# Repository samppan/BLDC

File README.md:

# BLDC

## BLDC Motor Driver Architecture
3 key building blocks for BLDC motor driver are: 
1. Motor controller, typically a MCU
2. Gate Drivers; PWM input, output drives half-bridges
3. Power MOSFET in half-bridges
4. Senseored feedback

<figcaption>Source: TI</figcaption>

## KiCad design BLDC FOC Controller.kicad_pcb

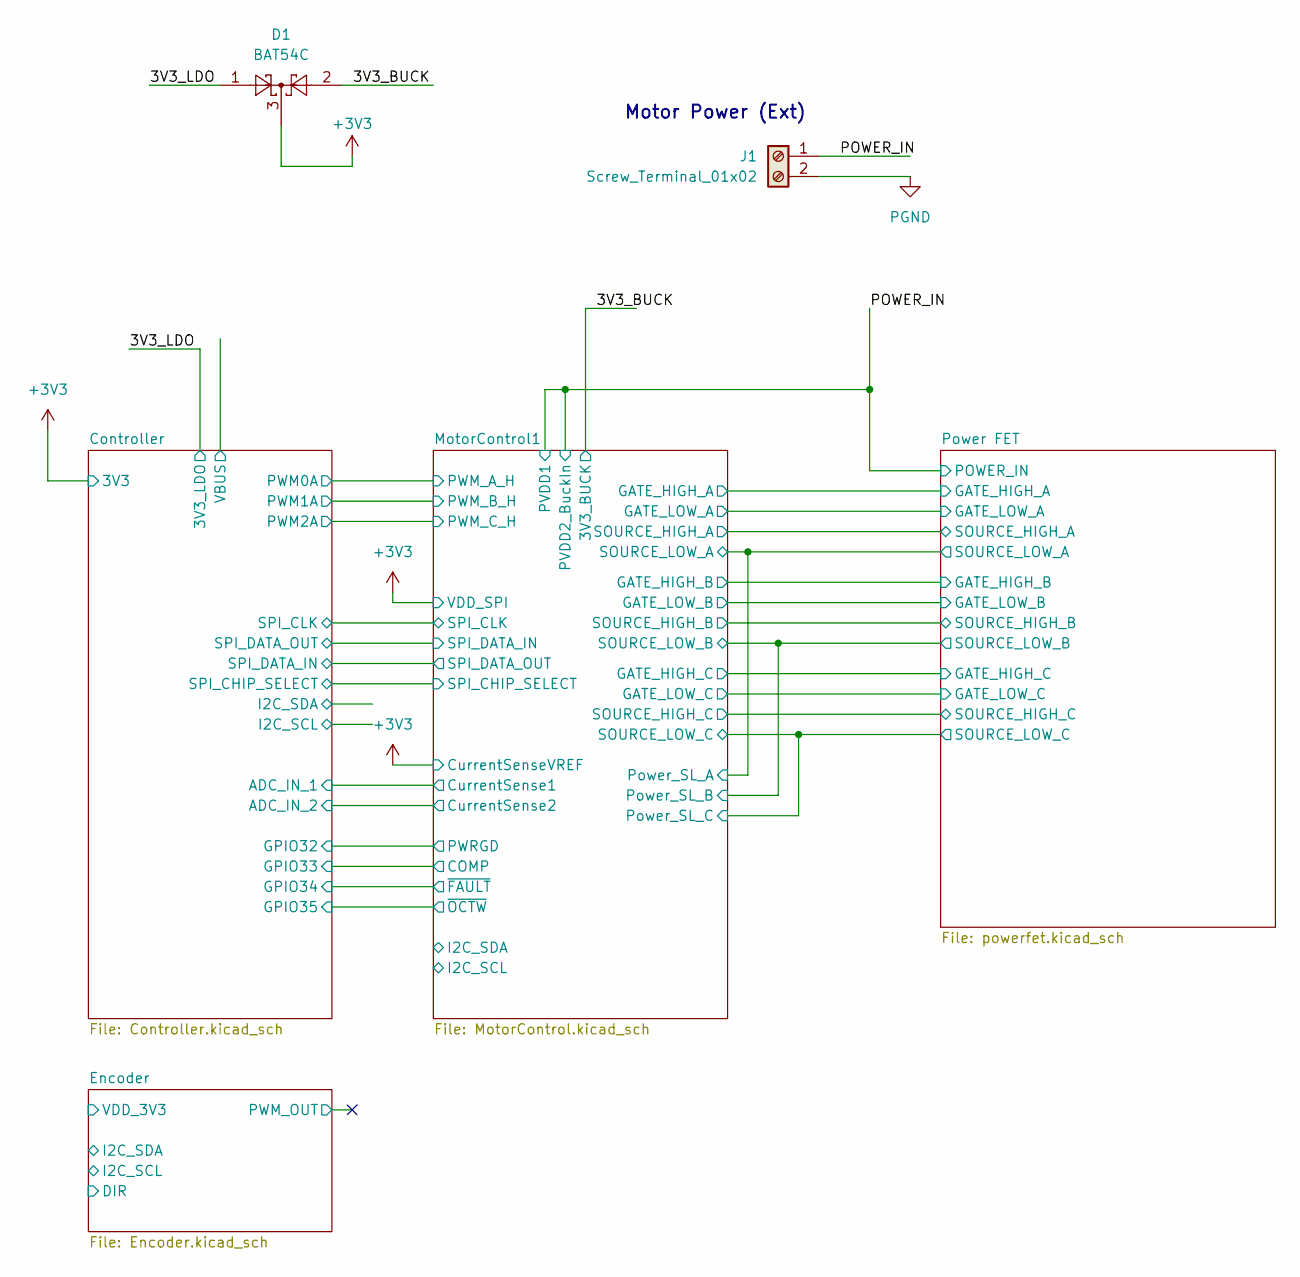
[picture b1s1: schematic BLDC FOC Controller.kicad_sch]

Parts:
D1: BAT54C; SOT-23
J1: Screw_Terminal_01x02; TerminalBlock_TE_282834-2_1x02_P2.54mm_Horizontal

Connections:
/3V3_BUCK: D1.2; also elsewhere on the board
/3V3_LDO: D1.1; also elsewhere on the board
/POWER_IN: J1.1; also elsewhere on the board
GNDA: J1.2; also elsewhere on the board

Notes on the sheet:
Motor Power (Ext)

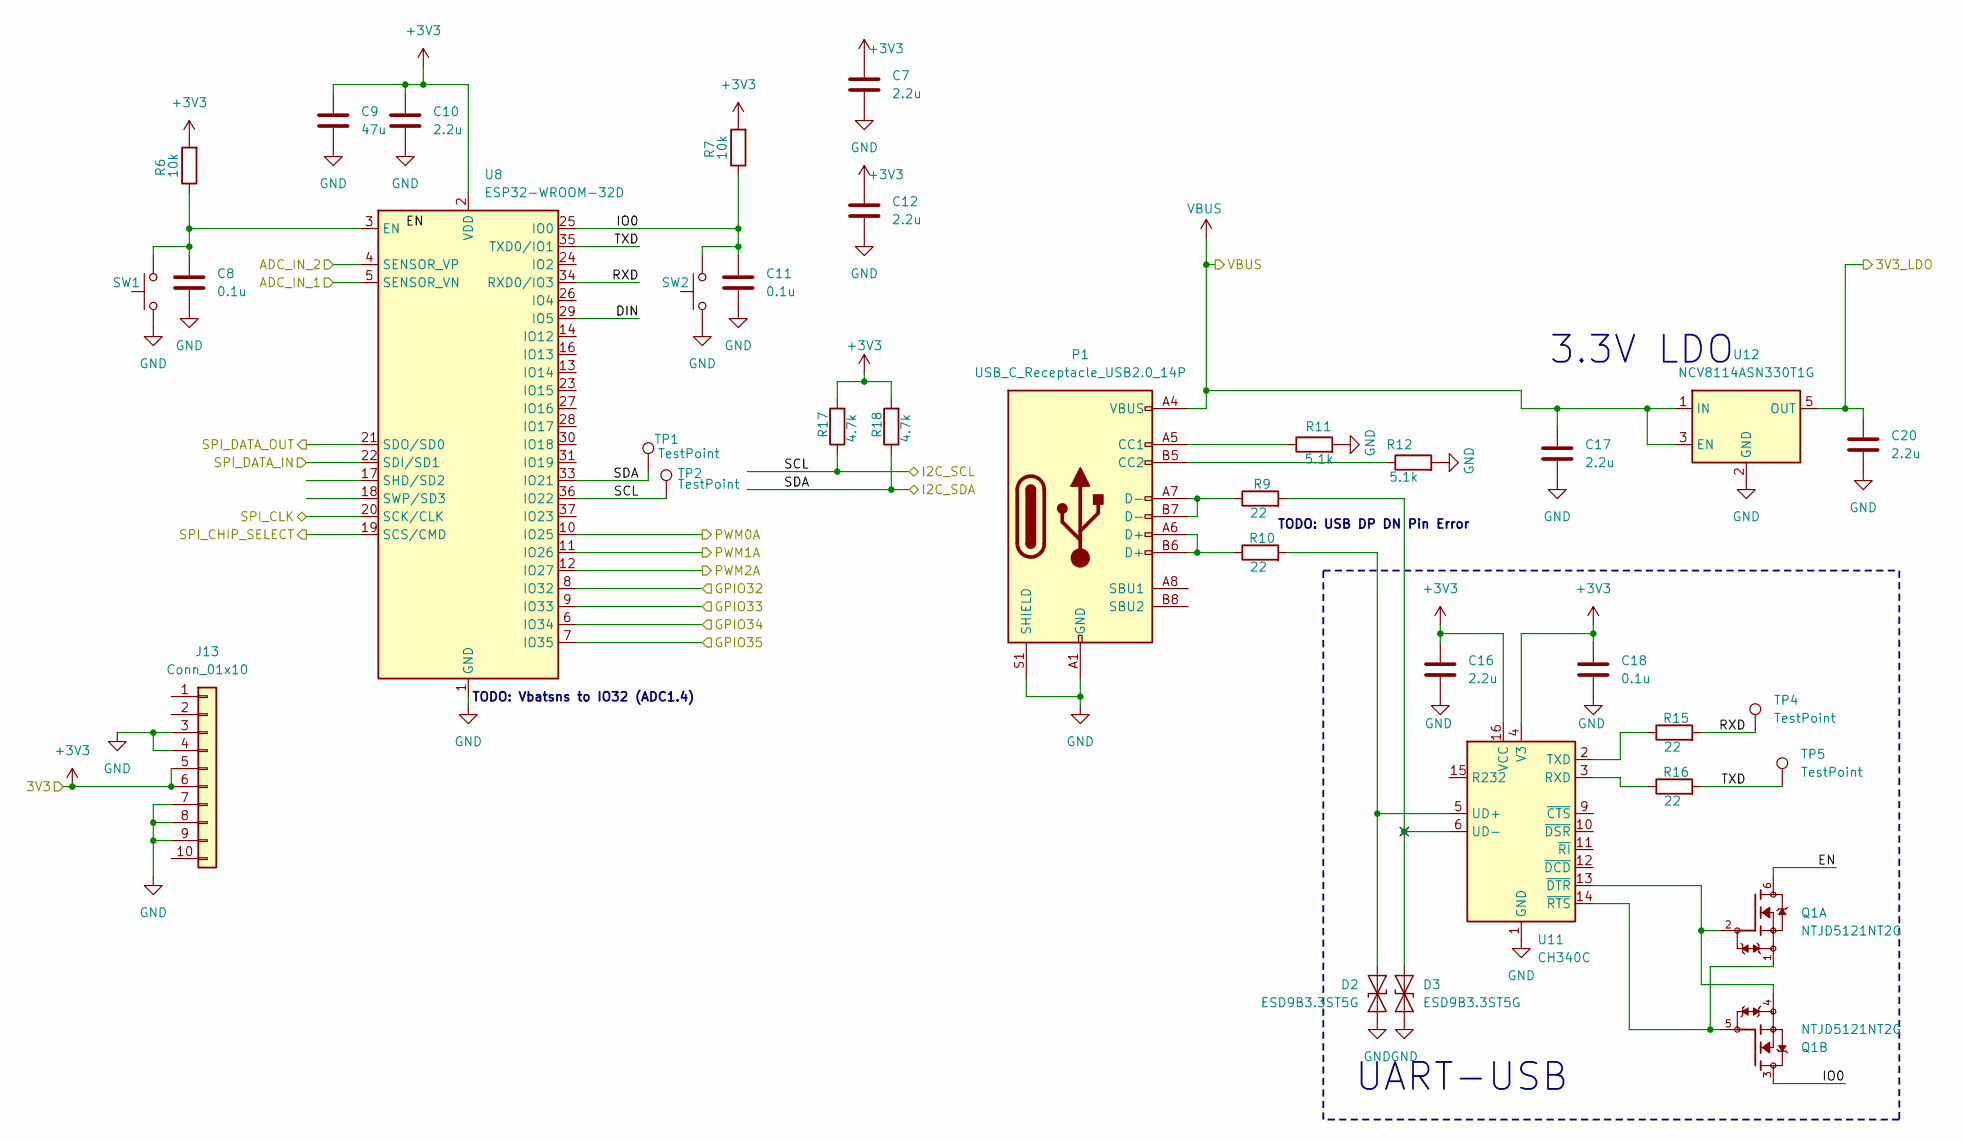
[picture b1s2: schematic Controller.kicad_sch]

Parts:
C7, C10, C12, C16, C17, C20: 2.2u; C_0603_1608Metric_Pad1.08x0.95mm_HandSolder
C8, C11, C18: 0.1u; C_0603_1608Metric_Pad1.08x0.95mm_HandSolder
C9: 47u; C_1206_3216Metric_Pad1.33x1.80mm_HandSolder
D2, D3: ESD9B3.3ST5G; D_SOD-923
J13: Conn_01x10; PinSocket_1x10_P2.54mm_Vertical
P1: USB_C_Receptacle_USB2.0_14P; USB_C_Receptacle_JAE_DX07S016JA1R1500
Q1: NTJD5121NT2G; SOT65P210X110-6N; PARTREV 9
R6, R7: 10k; R_0603_1608Metric_Pad0.98x0.95mm_HandSolder
R9, R10, R15, R16: 22; R_0603_1608Metric_Pad0.98x0.95mm_HandSolder
R11, R12: 5.1k; R_0603_1608Metric_Pad0.98x0.95mm_HandSolder
R17, R18: 4.7k; R_0603_1608Metric_Pad0.98x0.95mm_HandSolder
SW1, SW2: SW_Push_SPST_NO_Alps_SKRK
TP1, TP2, TP4, TP5: TestPoint; TestPoint_Pad_D1.5mm
U8: ESP32-WROOM-32D
U11: CH340C; SOIC-16_3.9x9.9mm_P1.27mm
U12: NCV8114ASN330T1G; TSOT-23-5

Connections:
/3V3_LDO: C20.1, U12.5 (OUT); also elsewhere on the board
/Controller/DIN: U8.29 (IO5)
/Controller/IO0: C11.1, Q1.3, R7.1, SW2.2, U8.25 (IO0)
/Controller/RXD: R15.2, TP4.1, U8.34 (RXD0/IO3)
/Controller/SCL: R17.1, TP2.1, U8.36 (IO22)
/Controller/SDA: R18.1, TP1.1, U8.33 (IO21)
/Controller/TXD: R16.2, TP5.1, U8.35 (TXD0/IO1)
/MotorControl1/COMP: U8.9 (IO33); also elsewhere on the board
/MotorControl1/INH_A: U8.10 (IO25); also elsewhere on the board
/MotorControl1/INH_B: U8.11 (IO26); also elsewhere on the board
/MotorControl1/INH_C: U8.12 (IO27); also elsewhere on the board
/MotorControl1/PWRGD: U8.8 (IO32); also elsewhere on the board
/MotorControl1/SCLK: U8.20 (SCK/CLK); also elsewhere on the board
/MotorControl1/SDI: U8.21 (SDO/SD0); also elsewhere on the board
/MotorControl1/SDO: U8.22 (SDI/SD1); also elsewhere on the board
/MotorControl1/SO1: U8.5 (SENSOR_VN); also elsewhere on the board
/MotorControl1/SO2: U8.4 (SENSOR_VP); also elsewhere on the board
/MotorControl1/~FAULT: U8.6 (IO34); also elsewhere on the board
/MotorControl1/~OCTW: U8.7 (IO35); also elsewhere on the board
/MotorControl1/~SCS: U8.19 (SCS/CMD); also elsewhere on the board
GND: C7.2, C8.2, C9.2, C10.2, C11.2, C12.2, C16.2, C17.2, C18.2, C20.2, D2.1 (A1), D3.1 (A1), J13.3, J13.4, J13.7, J13.8, J13.9, P1.A1 (GND), P1.A12 (GND), P1.B1 (GND), P1.B12 (GND), P1.S1 (SHIELD), R11.2, R12.2, SW1.1, SW2.1, U8.1 (GND), U8.15 (GND), U8.38 (GND), U8.39 (GND), U11.1 (GND), U12.2 (GND); also elsewhere on the board
unnamed: D2.2 (A2), R10.2, U11.5 (UD+)
unnamed: P1.A5 (CC1), R11.1
unnamed: P1.B5 (CC2), R12.1
unnamed: P1.A6 (D+), P1.B6 (D+), R10.1
unnamed: P1.A7 (D-), P1.B7 (D-), R9.1
unnamed: C8.1, R6.1, SW1.2, U8.3 (EN)
unnamed: R16.1, U11.3 (RXD)
unnamed: R15.1, U11.2 (TXD)
unnamed: Q1.2, Q1.4, U11.13 (~DTR)
unnamed: Q1.1, Q1.5, U11.14 (~RTS)
VBUS: C17.1, P1.A4 (VBUS), P1.A9 (VBUS), P1.B4 (VBUS), P1.B9 (VBUS), U12.1 (IN), U12.3 (EN)

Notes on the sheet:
UART-USB
3.3V LDO
TODO: Vbatsns to IO32 (ADC1.4)
TODO: USB DP DN Pin Error

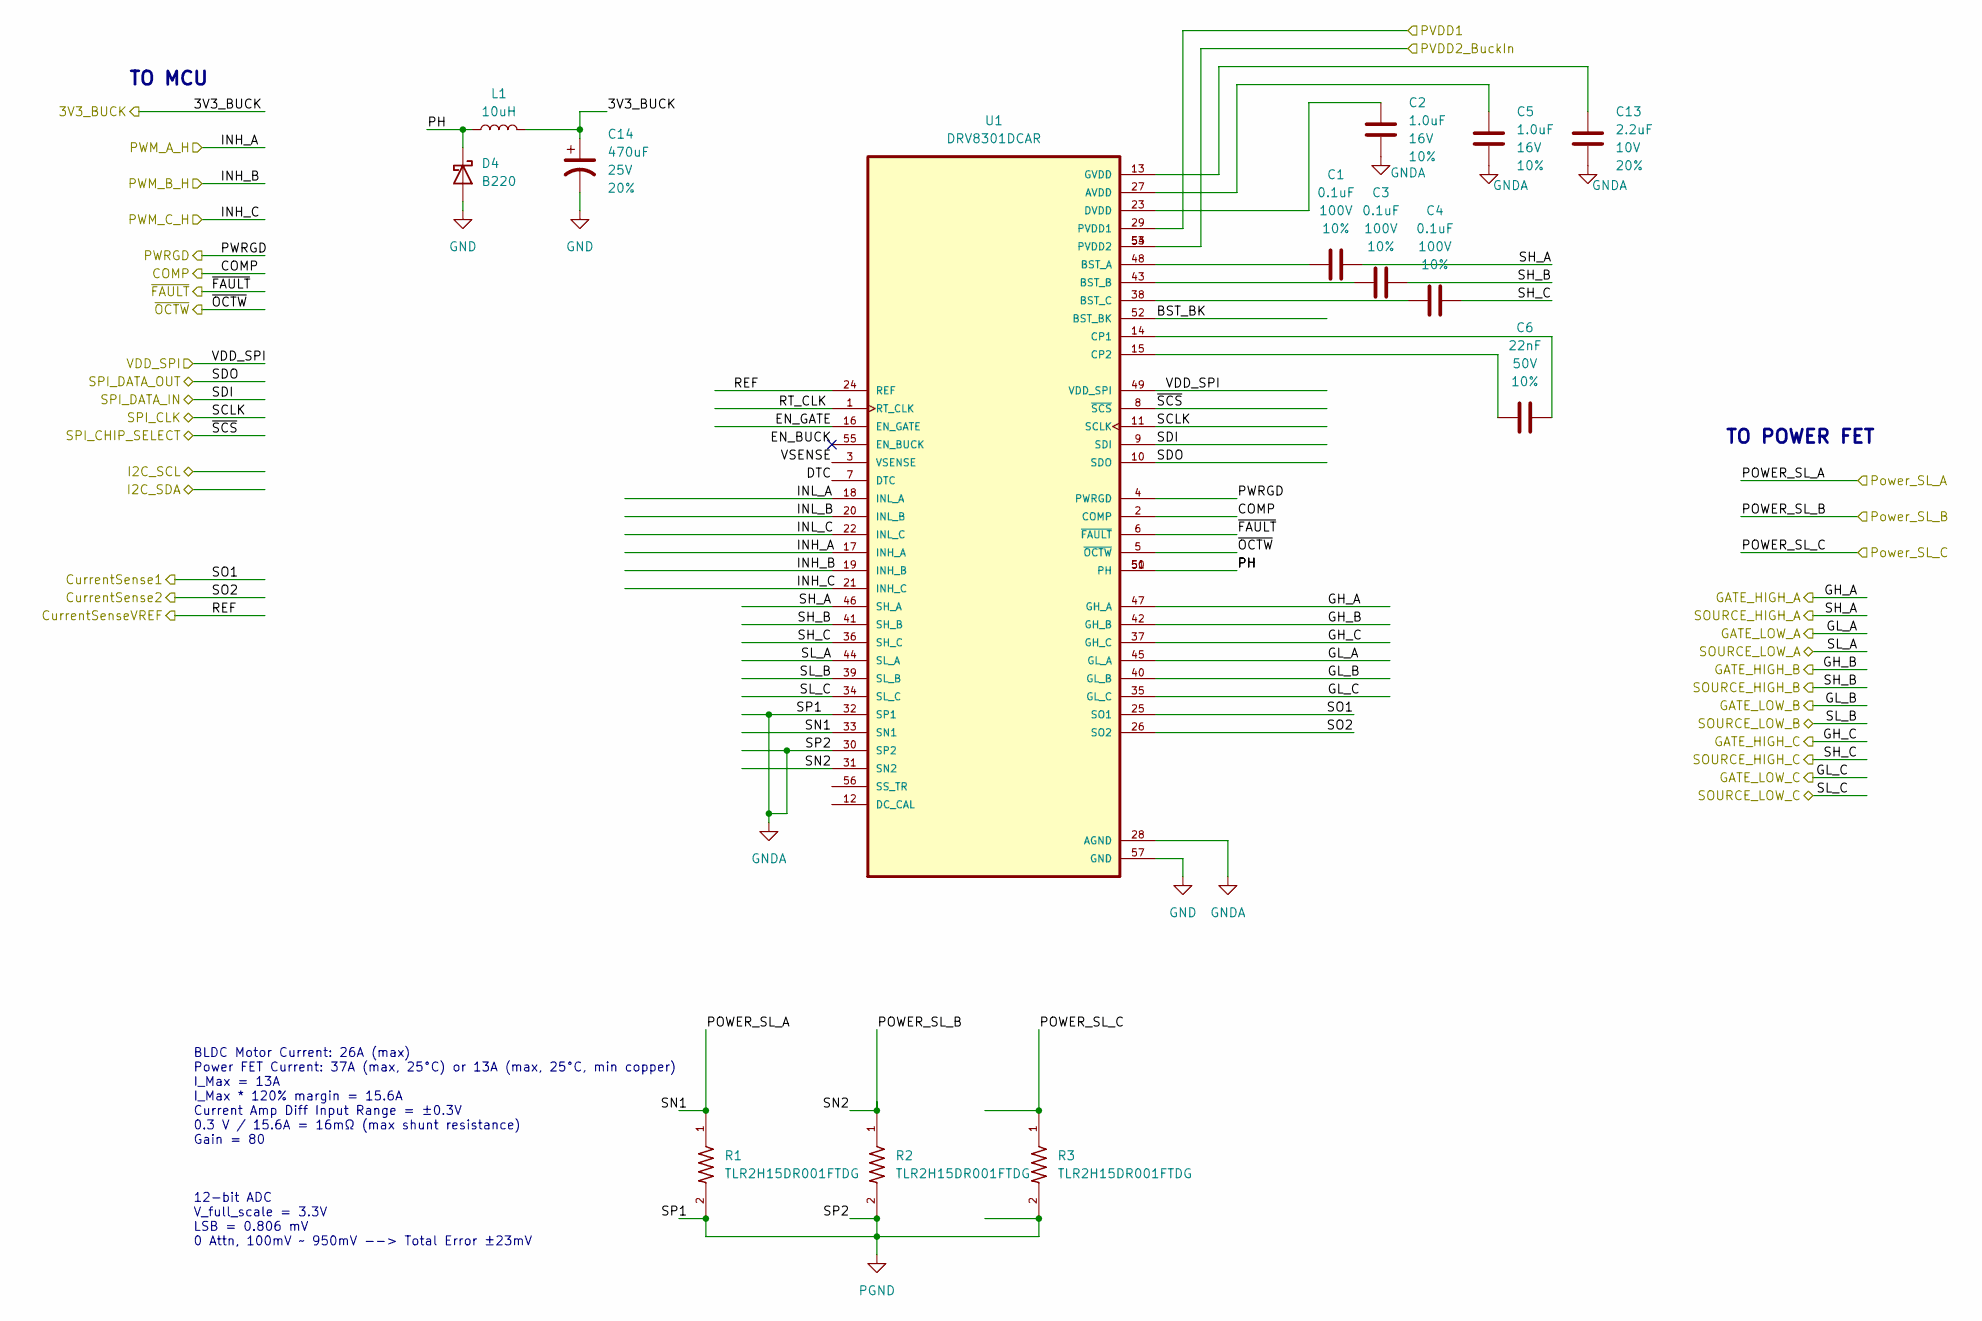
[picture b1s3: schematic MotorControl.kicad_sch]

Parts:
C1, C3, C4: 0.1uF; C_0603_1608Metric; Voltage 100V; Tolerance 10%
C2, C5: 1.0uF; C_0603_1608Metric; Voltage 16V; Tolerance 10%
C6: 22nF; C_0603_1608Metric; Voltage 50V; Tolerance 10%
C13: 2.2uF; C_0603_1608Metric_Pad1.08x0.95mm_HandSolder; Voltage 10V; Tolerance 20%
C14: 470uF; CP_Elec_10x10; Voltage 25V; Tolerance 20%
D4: B220; D_SMB
L1: 10uH; L_Taiyo-Yuden_NR-50xx_HandSoldering
R1, R2, R3: TLR2H15DR001FTDG; RESC5025X70N; Tolerance 1%
U1: DRV8301DCAR; HTSSOP-56-1EP_6.1x14mm_P0.5mm_EP3.61x6.35mm; PARTREV F

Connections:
/3V3_BUCK: C14.1, L1.2; also elsewhere on the board
/MotorControl1/BST_BK: U1.52 (BST_BK)
/MotorControl1/COMP: U1.2 (COMP); also elsewhere on the board
/MotorControl1/DTC: U1.7 (DTC)
/MotorControl1/EN_BUCK: U1.55 (EN_BUCK)
/MotorControl1/EN_GATE: U1.16 (EN_GATE)
/MotorControl1/GH_A: U1.47 (GH_A); also elsewhere on the board
/MotorControl1/GH_B: U1.42 (GH_B); also elsewhere on the board
/MotorControl1/GH_C: U1.37 (GH_C); also elsewhere on the board
/MotorControl1/GL_A: U1.45 (GL_A); also elsewhere on the board
/MotorControl1/GL_B: U1.40 (GL_B); also elsewhere on the board
/MotorControl1/GL_C: U1.35 (GL_C); also elsewhere on the board
/MotorControl1/INH_A: U1.17 (INH_A); also elsewhere on the board
/MotorControl1/INH_B: U1.19 (INH_B); also elsewhere on the board
/MotorControl1/INH_C: U1.21 (INH_C); also elsewhere on the board
/MotorControl1/INL_A: U1.18 (INL_A)
/MotorControl1/INL_B: U1.20 (INL_B)
/MotorControl1/INL_C: U1.22 (INL_C)
/MotorControl1/PH: D4.1 (K), L1.1, U1.50 (PH), U1.51 (PH)
/MotorControl1/POWER_SL_A: R1.1, U1.33 (SN1), U1.44 (SL_A); also elsewhere on the board
/MotorControl1/POWER_SL_C: R3.1, U1.34 (SL_C); also elsewhere on the board
/MotorControl1/PWRGD: U1.4 (PWRGD); also elsewhere on the board
/MotorControl1/RT_CLK: U1.1 (RT_CLK)
/MotorControl1/SCLK: U1.11 (SCLK); also elsewhere on the board
/MotorControl1/SDI: U1.9 (SDI); also elsewhere on the board
/MotorControl1/SDO: U1.10 (SDO); also elsewhere on the board
/MotorControl1/SH_A: C1.2, U1.46 (SH_A); also elsewhere on the board
/MotorControl1/SH_B: C3.2, U1.41 (SH_B); also elsewhere on the board
/MotorControl1/SH_C: C4.2, U1.36 (SH_C); also elsewhere on the board
/MotorControl1/SO1: U1.25 (SO1); also elsewhere on the board
/MotorControl1/SO2: U1.26 (SO2); also elsewhere on the board
/MotorControl1/VSENSE: U1.3 (VSENSE)
/MotorControl1/~FAULT: U1.6 (~FAULT); also elsewhere on the board
/MotorControl1/~OCTW: U1.5 (~OCTW); also elsewhere on the board
/MotorControl1/~SCS: U1.8 (~SCS); also elsewhere on the board
/POWER_IN: U1.29 (PVDD1), U1.53 (PVDD2), U1.54 (PVDD2); also elsewhere on the board
GND: C14.2, D4.2 (A), U1.57 (GND); also elsewhere on the board
GNDA: C2.2, C5.2, C13.2, R1.2, R2.2, R3.2, U1.28 (AGND), U1.30 (SP2), U1.32 (SP1); also elsewhere on the board
unnamed: C5.1, U1.27 (AVDD)
unnamed: C1.1, U1.48 (BST_A)
unnamed: C3.1, U1.43 (BST_B)
unnamed: C4.1, U1.38 (BST_C)
unnamed: C6.1, U1.14 (CP1)
unnamed: C6.2, U1.15 (CP2)
unnamed: C2.1, U1.23 (DVDD)
unnamed: C13.1, U1.13 (GVDD)

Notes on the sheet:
BLDC Motor Current: 26A (max) Power FET Current: 37A (max, 25°C) or 13A (max, 25°C, min copper) I_Max = 13A I_Max * 120% margin = 15.6A Current Amp Diff Input Range = ±0.3V 0.3 V / 15.6A = 16mΩ (max shunt resistance) Gain = 80 12-bit ADC V_full_scale = 3.3V LSB = 0.806 mV 0 Attn, 100mV ~ 950mV --> 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
TO MCU
TO POWER FET

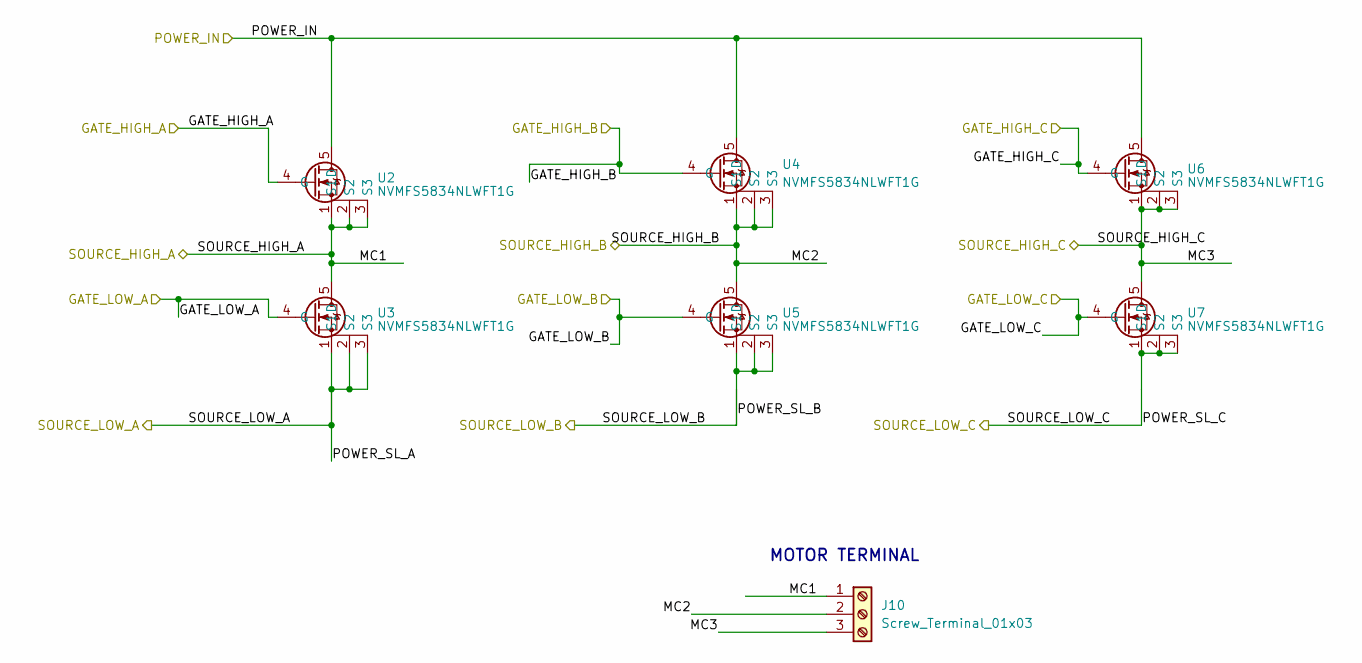
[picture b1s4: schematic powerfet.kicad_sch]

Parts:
J10: Screw_Terminal_01x03; TerminalBlock_TE_282834-3_1x03_P2.54mm_Horizontal
U2, U3, U4, U5, U6, U7: NVMFS5834NLWFT1G; TRANS_NVMFS5834NLWFT1G

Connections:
/MotorControl1/GH_A: U2.4 (G); also elsewhere on the board
/MotorControl1/GH_B: U4.4 (G); also elsewhere on the board
/MotorControl1/GH_C: U6.4 (G); also elsewhere on the board
/MotorControl1/GL_A: U3.4 (G); also elsewhere on the board
/MotorControl1/GL_B: U5.4 (G); also elsewhere on the board
/MotorControl1/GL_C: U7.4 (G); also elsewhere on the board
/MotorControl1/POWER_SL_A: U3.1 (S1), U3.2 (S2), U3.3 (S3); also elsewhere on the board
/MotorControl1/POWER_SL_C: U7.1 (S1), U7.2 (S2), U7.3 (S3); also elsewhere on the board
/MotorControl1/SH_A: J10.1, U2.1 (S1), U2.2 (S2), U2.3 (S3), U3.5 (D); also elsewhere on the board
/MotorControl1/SH_B: J10.2, U4.1 (S1), U4.2 (S2), U4.3 (S3), U5.5 (D); also elsewhere on the board
/MotorControl1/SH_C: J10.3, U6.1 (S1), U6.2 (S2), U6.3 (S3), U7.5 (D); also elsewhere on the board
/POWER_IN: U2.5 (D), U4.5 (D), U6.5 (D); also elsewhere on the board

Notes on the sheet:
MOTOR TERMINAL

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
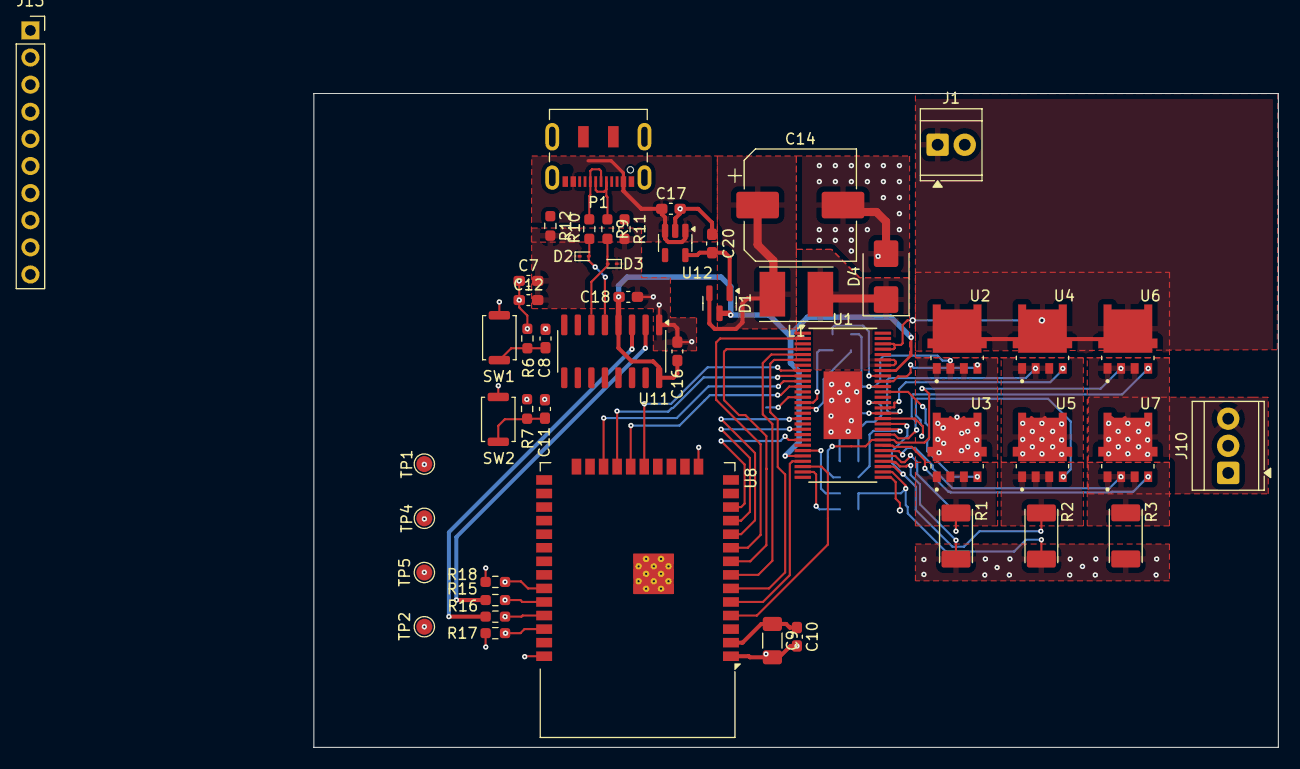
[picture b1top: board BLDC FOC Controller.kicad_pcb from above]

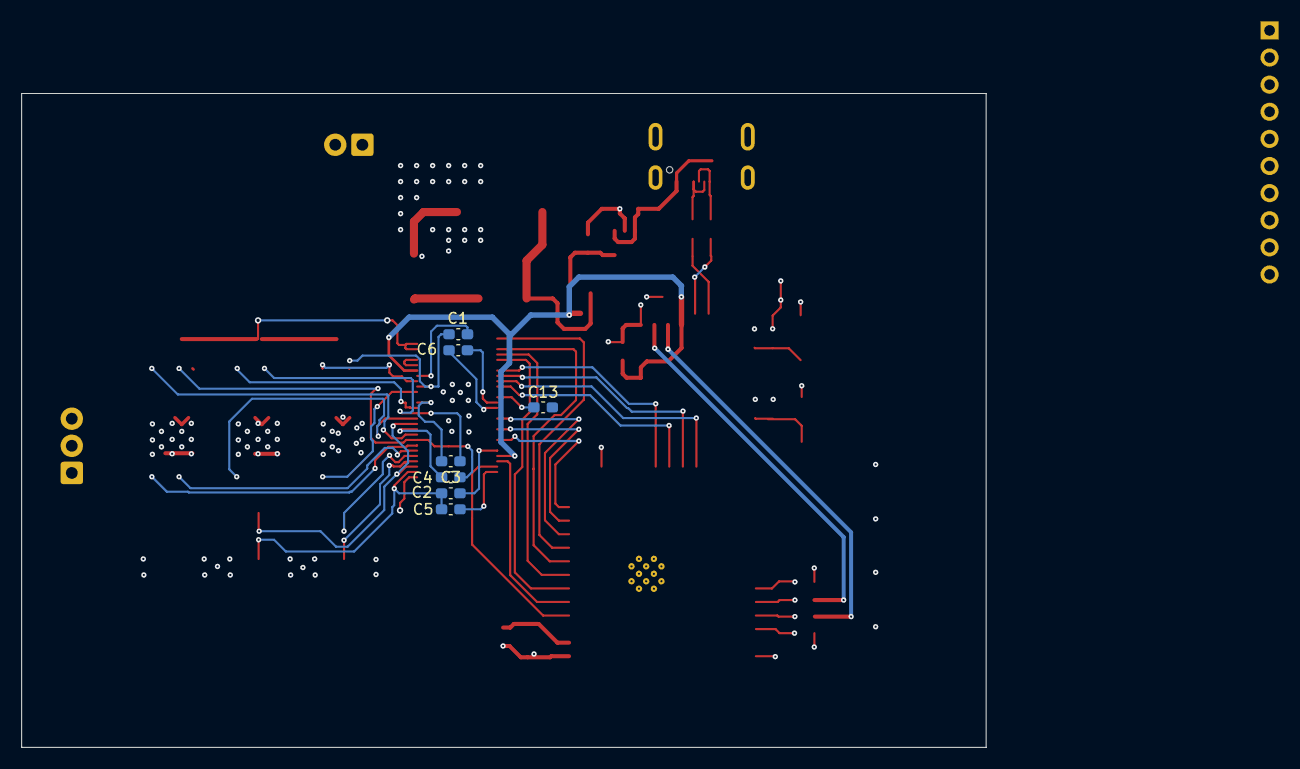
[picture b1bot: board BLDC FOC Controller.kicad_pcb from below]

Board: 4 copper layers, 90.3 x 61.2 mm, 56 parts (7 on the bottom side), 54 nets.

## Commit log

2021-11-22 Create LICENSE
    add MIT license from license template default
2025-04-10 init commit with version control
